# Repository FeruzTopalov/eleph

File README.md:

# **ELEPH** - _Never Get Lost!_

> **Note**
> Development of this device has been finished, only bug-fixes in the FW are possible
> There is an improved version of this device being under development, please see <https://github.com/FeruzTopalov/spoke>

<p align="center">
  <i>Dedicated to my friend Alexander Sadaev, rock climber.</i>
</p>

Eleph is a GPS-based Local Relative Navigation System (LRNS) for group of up to 6 members. It allows you to share your positional data in **real-time** among other Eleph-devices and navigate to each of them in a relative manner by providing **Distance** and **Azimuth** information - like RADAR does.

## Demonstration

Before diving into the details, watch the demo on **YouTube**: <https://youtu.be/EMacKdg9Z_0>

## Problem & Solution

As long as you stay under cell-coverage a navigation, either absolute or relative, is not a problem at all. You just use your phone with maps and messengers to find or share locations. Things change when you go off-grid. Hiking, skiing, sailing or whatever outdoor activity are a potential place to lose sight of your teammates. How to navigate in the group? Hopefully, there are couple of solutions available on the market:

* [LynQ](https://lynqme.com/pages/dev-consumer)
* [XQUAD](https://www.indiegogo.com/projects/xquad-smart-location-tracking-without-phones#/)
* [GoFindMe](https://www.indiegogo.com/projects/gofindme-a-gps-tracker-works-without-cell-service/#/)
* [GoTenna](https://gotennamesh.com/products/mesh)
* Also [GARMIN Dog collar](https://buy.garmin.com/en-US/US/c12522-p1.html)
* Also any [AIS](https://en.wikipedia.org/wiki/Automatic_identification_system) system

unfortunately all of them are commercial. But not the **Eleph**! 

**Eleph** is _open-source/open-hardware_ device which contains all major features needed for group navigation, such as:

* Detailed absolute positional information about each device in group
* RADAR-like interface with relative positional information about each device in group
* Memory slots to hold the position of any device and navigate it later
* GeoFence feature
* Timeout feature
* Alarm button

Due to open-source and simple and cheap hardware, Eleph is highly flexible solution that could be adapted to any use case you want:

* Hiking
* Climbing
* Sailing
* Hunting with the dogs
* Assets tracking
* and more...

## Technology

Eleph is written in pure C and runs on STM32 microcontroller. It has GPS module to receive positional data and synchronization signal, radio transceiver to exchange with radio packets between other devices, graphical display to show information on it, EEPROM memory IC to store coordinates, tactile buttons to control the device, buzzer to notify about events and couple of LEDs.

GPS module provides NMEA-0183 stream at 9600 baud. Microcontroller process the stream using DMA and parse it. Fields being extracted are RMC, GGA, GSA, GSV. Those give us information about time, date, latitude, longitude, speed, course, altitude, satellites in view and in use, navigation mode and validness of data.

GPS module also provides time synchronization signal - PPS. It is used as a time reference for the transmitting and receiving radio packets inside a current group of devices. Each group operates at the specific frequency channel, the way like regular radios. Each device in a group has unique predefined number from 1 to 6, so there are 6 members in a group maximum. Eleph uses TDMA technique to give channel access for each group member, so the device number corresponds to the time-slot occupied by device. There are 125 ms timer which starts counting from the rise of the PPS pulse. First 125 ms time-slot is used to parse and prepare positional data of the device. Next six time-slots are used to exchange with the positional data between devices via radio. A device is in TX state when time-slot number is equal to the device number, and in RX state otherwise. Remaining time before next PPS is reserved for relative positions calculation and displaying the results.

Eleph uses FSK transceiver and operates in LPD 433 MHz band (please make sure you are allowed to use those frequencies in your region, change otherwise). Data rate is 2400 bps, deviation is 2400 Hz (mod index = 2), channel spacing is 25 kHz. Packet structure is shown below. It consist of 29 bytes total and takes ~97 ms to be transmitted over-the-air.

In order to calculate relative positions of other devices, Eleph uses two formulas. First one is [Haversine formula](https://en.wikipedia.org/wiki/Haversine_formula) which determines the distance between two points on a sphere. The second one is [Loxodrome formula](https://en.wikipedia.org/wiki/Rhumb_line) which determines bearing to a point on a sphere relative to true north. All calculations are performed with a highest possible, double precision, so the results are in a great agreement with my simulations on PC. Precision of the formulas is another matter. It is known that haversine formula is numerically better-conditioned for small distances, but on the other side it doesn't take into account ellipsoidness of the Earth and uses it's mean radius. Also it is known that loxodrome (or rhumb line) shows not-the-shortest way to reach point of interest (the shortest way is provided by orthodrome, or great circle route), but the constant bearing, which is more useful in practice. Anyway, my simulations using Google Earth Pro ruler leave me no concerns about accuracy of used formulas. According to them the error for both is less than 1% as long as the distance is smaller than 300 km (!).

<p align="center">
  <i>(courtesy of <a href="https://www.esri.com/arcgis-blog/products/product/mapping/mercators-500th-birthday/">ESRI</a>)</i>
</p>

---

## FAQ

* _**Why is it called Eleph?**_ -Eleph stands for elephant. Elephants are a social animals, they form close bonds and stay in-touch - that is the main aim of the Eleph device.
* _**Why no LoRa yet?**_ -Believe or not, but i see no reason to use LoRa in the Eleph right now. Mainly due to low data rate. Probably next time, when i shorten payload, i will switch to LoRa mode.
* _**Why there is no compass?**_ -When i started the project i thought that COG (Course over Ground) information from the GPS would be enough, and that the COG relates to the true north, while compass gives magnetic north. Obviously information about true north is more valuable. The drawback for now is that COG requires you to move, there is no way to find the direction standing still.
* _**Any plans to resume the project?**_ -Next milestone is to rework user interface, make it simpler; refuse from excessive payload information, leaving just Lat/Lon data; update schematic/hardware. 
* _**How can i support the project?**_ -Eleph really needs your support. Main functionality is tested, but full and comprehensive outdoor tests are nor performed well yet. You could build it, test it on your side and report an issue if so - that is the best way to support.

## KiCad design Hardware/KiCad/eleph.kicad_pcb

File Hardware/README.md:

# Eleph Hardware
This folder contains hardware design of the ELEPH

## Design files
In the "**KiCad**" folder you can find KiCad project of the Eleph.

## Schematic
In the "**Schematic**" folder you can find PDF file with the schematic diagram.

## Production files
In the "**Gerbers**" folder you can find production files of Eleph.

## Hardware Notes
Couple of words about power supply. Supply chain is **_Single 18650 -> LDO 3.3V_**. I found no reason to put DC/DC because in common they have 80%-90% of efficiency, while LDO has ~78% in worst case (3.3V / 4.2V = 0.78). Do the increased complexity and cost worth several percent of efficiency? I do not think so.

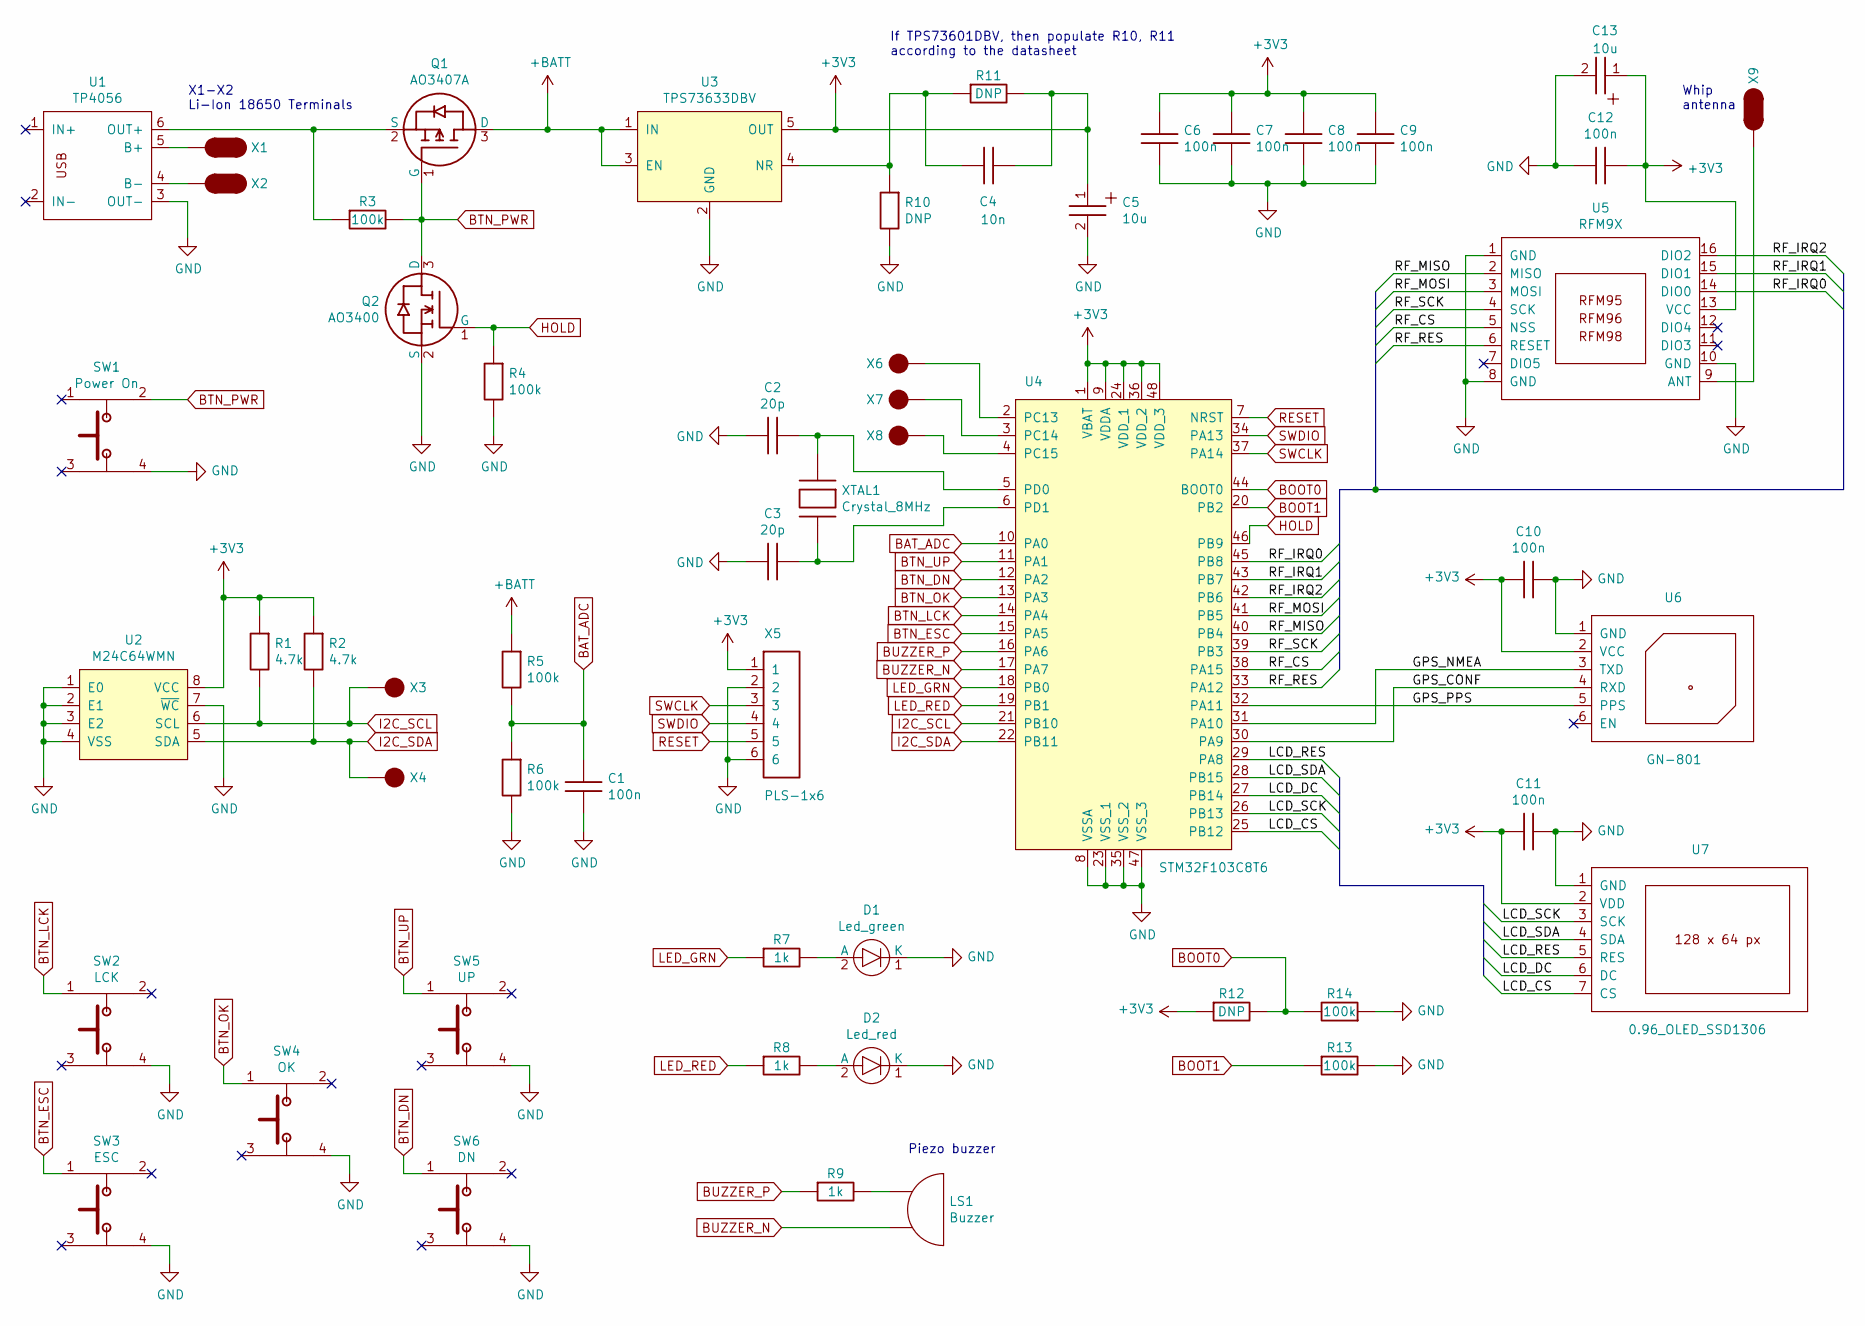
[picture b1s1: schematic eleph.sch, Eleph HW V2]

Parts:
C1, C6, C7, C8, C9, C10, C11, C12: 100n; C0805
C2, C3: 20p; C0805
C4: 10n; C0805
C5, C13: 10u; C_tantA
D1: Led_green; D1206
D2: Led_red; D1206
LS1: Buzzer; Buzzer_pitch7.6mm
Q1: AO3407A; SOT-23
Q2: AO3400; SOT-23
R1, R2: 4.7k; R0805
R3, R4, R5, R6, R13, R14: 100k; R0805
R7, R8, R9: 1k; R0805
R10, R11, R12: DNP; R0805
SW1: Power On; 52x52switch_smd_lowprofile
SW2: LCK; 6x6switch_smd
SW3: ESC; 6x6switch_smd
SW4: OK; 6x6switch_smd
SW5: UP; 6x6switch_smd
SW6: DN; 6x6switch_smd
U1: TP4056
U2: M24C64WMN; SOIC-8
U3: TPS73633DBV; SOT-23-5
U4: STM32F103C8T6; LQFP-48
U5: RFM9X
U6: GN-801
U7: 0.96_OLED_SSD1306; 0.96_OLED_SSD1306_7pin
X1, X2: Pad_oval
X3, X4, X6, X7, X8: Pad_round
X5: PLS-1x6; 1x6header
X9: Pad_oval; Antenna_terminal
XTAL1: Crystal_8MHz; HC49SM

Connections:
+3V3: C4.1, C5.1, C6.1, C7.1, C8.1, C9.1, C10.1, C11.1, C12.2, C13.1, R1.1, R2.1, R11.2, R12.1, U2.8 (VCC), U3.5 (OUT), U4.1 (VBAT), U4.9 (VDDA), U4.24 (VDD_1), U4.36 (VDD_2), U4.48 (VDD_3), U5.13 (VCC), U6.2 (VCC), U7.2 (VDD), X5.1
+BATT: Q1.3 (D), R5.1, U3.1 (IN), U3.3 (EN)
/GPS_CONF: U4.30 (PA9), U6.4 (RXD)
/GPS_NMEA: U4.31 (PA10), U6.3 (TXD)
/GPS_PPS: U4.32 (PA11), U6.5 (PPS)
/LCD_CS: U4.25 (PB12), U7.7 (CS)
/LCD_DC: U4.27 (PB14), U7.6 (DC)
/LCD_RES: U4.29 (PA8), U7.5 (RES)
/LCD_SCK: U4.26 (PB13), U7.3 (SCK)
/LCD_SDA: U4.28 (PB15), U7.4 (SDA)
/RF_CS: U4.38 (PA15), U5.5 (NSS)
/RF_IRQ0: U4.45 (PB8), U5.14 (DIO0)
/RF_IRQ1: U4.43 (PB7), U5.15 (DIO1)
/RF_IRQ2: U4.42 (PB6), U5.16 (DIO2)
/RF_MISO: U4.40 (PB4), U5.2 (MISO)
/RF_MOSI: U4.41 (PB5), U5.3 (MOSI)
/RF_RES: U4.33 (PA12), U5.6 (RESET)
/RF_SCK: U4.39 (PB3), U5.4 (SCK)
BAT_ADC: C1.1, R5.2, R6.1, U4.10 (PA0)
BOOT0: R12.2, R14.2, U4.44 (BOOT0)
BOOT1: R13.1, U4.20 (PB2)
BTN_DN: SW6.1, U4.12 (PA2)
BTN_ESC: SW3.1, U4.15 (PA5)
BTN_LCK: SW2.1, U4.14 (PA4)
BTN_OK: SW4.1, U4.13 (PA3)
BTN_PWR: Q1.1 (G), Q2.3 (D), R3.2, SW1.2
BTN_UP: SW5.1, U4.11 (PA1)
BUZZER_N: LS1.2, U4.17 (PA7)
BUZZER_P: R9.1, U4.16 (PA6)
GND: C1.2, C2.1, C3.1, C5.2, C6.2, C7.2, C8.2, C9.2, C10.2, C11.2, C12.1, C13.2, D1.1 (K), D2.1 (K), Q2.2 (S), R4.2, R6.2, R10.2, R13.2, R14.1, SW1.4, SW2.4, SW3.4, SW4.4, SW5.4, SW6.4, U1.3 (OUT-), U2.1 (E0), U2.2 (E1), U2.3 (E2), U2.4 (VSS), U2.7 (~WC), U3.2 (GND), U4.8 (VSSA), U4.23 (VSS_1), U4.35 (VSS_2), U4.47 (VSS_3), U5.1 (GND), U5.8 (GND), U5.10 (GND), U6.1 (GND), U7.1 (GND), X5.2, X5.6
HOLD: Q2.1 (G), R4.1, U4.46 (PB9)
I2C_SCL: R1.2, U2.6 (SCL), U4.21 (PB10), X3.1
I2C_SDA: R2.2, U2.5 (SDA), U4.22 (PB11), X4.1
LED_GRN: R7.1, U4.18 (PB0)
LED_RED: R8.1, U4.19 (PB1)
unnamed: C2.2, U4.5 (PD0), XTAL1.1
unnamed: C3.2, U4.6 (PD1), XTAL1.2
unnamed: C4.2, R10.1, R11.1, U3.4 (NR)
unnamed: D1.2 (A), R7.2
unnamed: D2.2 (A), R8.2
unnamed: LS1.1, R9.2
unnamed: Q1.2 (S), R3.1, U1.6 (OUT+)
unnamed: U1.4 (B-), X2.1
unnamed: U1.5 (B+), X1.1
unnamed: U4.2 (PC13), X6.1
unnamed: U4.3 (PC14), X7.1
unnamed: U4.4 (PC15), X8.1
unnamed: U5.9 (ANT), X9.1
RESET: U4.7 (NRST), X5.5
SWCLK: U4.37 (PA14), X5.3
SWDIO: U4.34 (PA13), X5.4

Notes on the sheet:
X1-X2 Li-Ion 18650 Terminals
If TPS73601DBV, then populate R10, R11 according to the datasheet
Whip antenna
Piezo buzzer

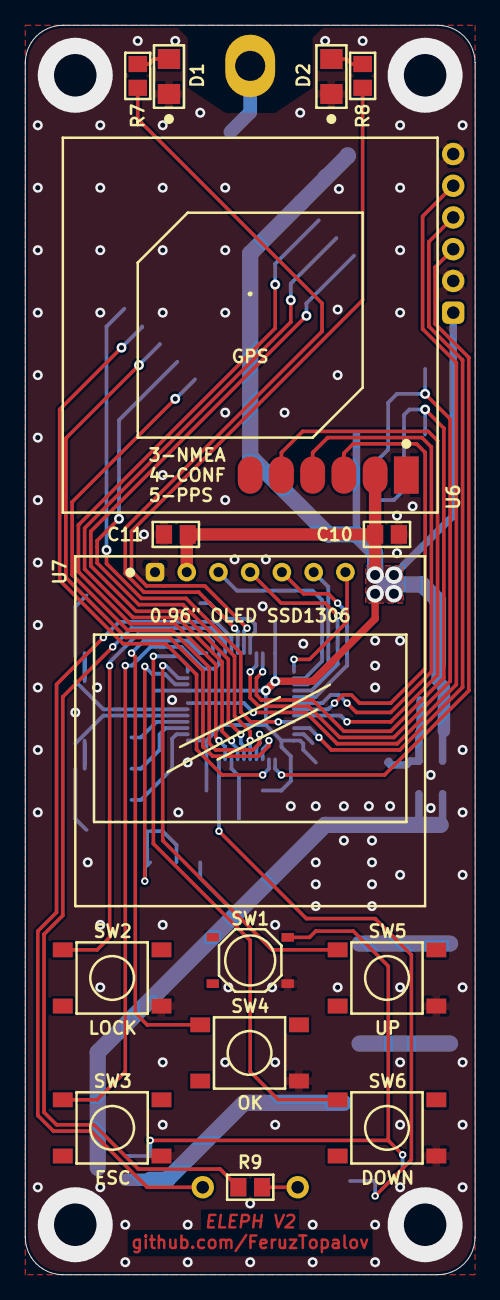
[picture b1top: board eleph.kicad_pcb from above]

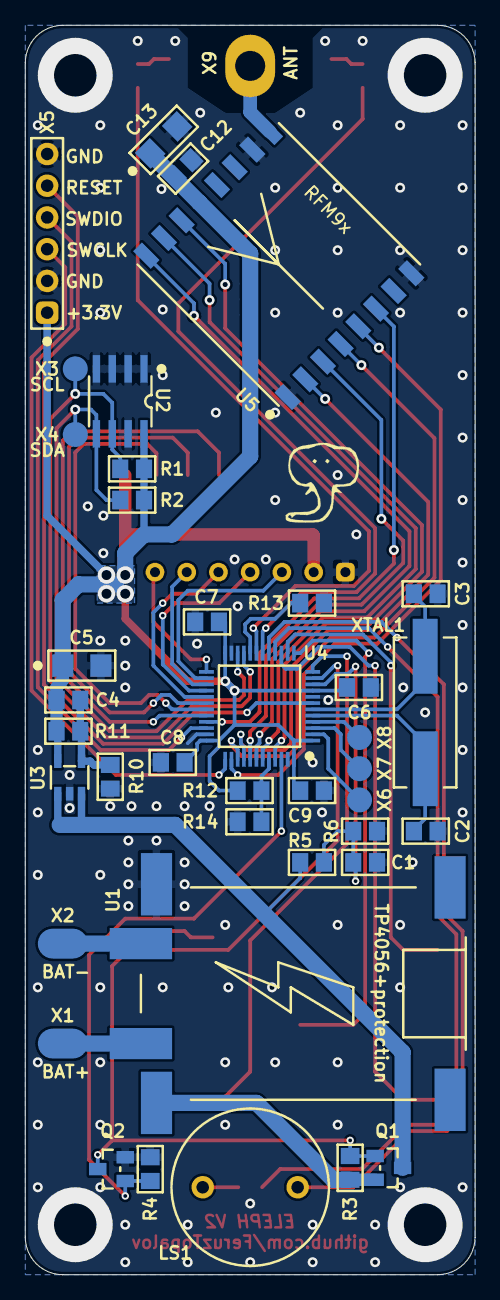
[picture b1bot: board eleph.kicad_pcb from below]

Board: 2 copper layers, 36.0 x 100.0 mm, 55 parts (40 on the bottom side), 51 nets.

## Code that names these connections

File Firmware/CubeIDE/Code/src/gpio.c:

/*
    ELEPH - Local Relative Navigation System <https://github.com/FeruzTopalov/eleph/>

	Copyright (C) 2021 Feruz Topalov
	Released under the GNU General Public License v3.0 <https://www.gnu.org/licenses/>
    
    file: gpio.c
*/



#include "stm32f10x.h"
#include "gpio.h"



//Initialization of all used ports
void gpio_init(void)
{
    //Port A
    RCC->APB2ENR |= RCC_APB2ENR_IOPAEN;
    
    //PA0 - ADC0 (Battery voltage)
    GPIOA->CRL &= ~GPIO_CRL_MODE0;      //input mode
    GPIOA->CRL &= ~GPIO_CRL_CNF0;       //analog input
    
    //PA1 - Button UP
    GPIOA->CRL &= ~GPIO_CRL_MODE1;      //input mode
    GPIOA->CRL &= ~GPIO_CRL_CNF1_0;     //input with pull
    GPIOA->CRL |= GPIO_CRL_CNF1_1; 
    GPIOA->ODR |= GPIO_ODR_ODR1;        //pull-up on
    
    //PA2 - Button DOWN
    GPIOA->CRL &= ~GPIO_CRL_MODE2;      //input mode
    GPIOA->CRL &= ~GPIO_CRL_CNF2_0;     //input with pull
    GPIOA->CRL |= GPIO_CRL_CNF2_1; 
    GPIOA->ODR |= GPIO_ODR_ODR2;        //pull-up on
    
    //PA3 - Button OK
    GPIOA->CRL &= ~GPIO_CRL_MODE3;      //input mode
    GPIOA->CRL &= ~GPIO_CRL_CNF3_0;     //input with pull
    GPIOA->CRL |= GPIO_CRL_CNF3_1; 
    GPIOA->ODR |= GPIO_ODR_ODR3;        //pull-up on
    
    //PA4 - Button LOCK
    GPIOA->CRL &= ~GPIO_CRL_MODE4;      //input mode
    GPIOA->CRL &= ~GPIO_CRL_CNF4_0;     //input with pull
    GPIOA->CRL |= GPIO_CRL_CNF4_1; 
    GPIOA->ODR |= GPIO_ODR_ODR4;        //pull-up on
    
    //PA5 - Button ESC
    GPIOA->CRL &= ~GPIO_CRL_MODE5;      //input mode
    GPIOA->CRL &= ~GPIO_CRL_CNF5_0;     //input with pull
    GPIOA->CRL |= GPIO_CRL_CNF5_1; 
    GPIOA->ODR |= GPIO_ODR_ODR5;        //pull-up on
    
    //PA6 - Piezo Buzzer (PWM) P
    GPIOA->CRL &= ~GPIO_CRL_MODE6_0;    //output 2 MHz
    GPIOA->CRL |= GPIO_CRL_MODE6_1;
    GPIOA->CRL &= ~GPIO_CRL_CNF6;       //alternate output push-pull
    GPIOA->CRL |= GPIO_CRL_CNF6_1;

    //PA7 - Piezo Buzzer (PWM) N
    GPIOA->CRL &= ~GPIO_CRL_MODE7_0;  	//output 2 MHz
    GPIOA->CRL |= GPIO_CRL_MODE7_1;
    GPIOA->CRL &= ~GPIO_CRL_CNF7_0;    	//alternate output push-pull
    GPIOA->CRL |= GPIO_CRL_CNF7_1;

    //PA8 - RES (SSD1306)
    GPIOA->CRH &= ~GPIO_CRH_MODE8_0;    //output 2 MHz
    GPIOA->CRH |= GPIO_CRH_MODE8_1;
    GPIOA->CRH &= ~GPIO_CRH_CNF8;      	//output push-pull
    
    //PA9 - USART TX1 (GPS config)
    GPIOA->CRH &= ~GPIO_CRH_MODE9_0;    //output 2 MHz
    GPIOA->CRH |= GPIO_CRH_MODE9_1;
    GPIOA->CRH &= ~GPIO_CRH_CNF9_0;     //alternate output push-pull
    GPIOA->CRH |= GPIO_CRH_CNF9_1;
    
    //PA10 - USART RX1 (GPS NMEA stream)
    GPIOA->CRH &= ~GPIO_CRH_MODE10;     //input
    GPIOA->CRH |= GPIO_CRH_CNF10_0;     //alternate input floating
    GPIOA->CRH &= ~GPIO_CRH_CNF10_1;
    
    //PA11 - GPS (PPS interrupt)
    GPIOA->CRH &= ~GPIO_CRH_MODE11;     //input mode
    GPIOA->CRH &= ~GPIO_CRH_CNF11_0;    //input with pull
    GPIOA->CRH |= GPIO_CRH_CNF11_1; 
    GPIOA->ODR &= ~GPIO_ODR_ODR11;      //pull-down
    
    //PA12 - RF Reset
    //GPIOA->CRH &= ~GPIO_CRH_MODE12_0;   //output 2 MHz
    //GPIOA->CRH |= GPIO_CRH_MODE12_1;
    //GPIOA->CRH &= ~GPIO_CRH_CNF12;		//output push-pull
    
    //PA15 - RF Chip Select
    GPIOA->CRH &= ~GPIO_CRH_MODE15_0;   //output 2 MHz
    GPIOA->CRH |= GPIO_CRH_MODE15_1;
    GPIOA->CRH &= ~GPIO_CRH_CNF15;      //output push-pull
    
    

    //Port B
    RCC->APB2ENR |= RCC_APB2ENR_IOPBEN;
    
    //PB0 - Green LED
    GPIOB->CRL &= ~GPIO_CRL_MODE0_0;    //output 2 MHz
    GPIOB->CRL |= GPIO_CRL_MODE0_1;
    GPIOB->CRL &= ~GPIO_CRL_CNF0;       //output push-pull
    
    //PB1 - Red LED
    GPIOB->CRL &= ~GPIO_CRL_MODE1_0;    //output 2 MHz
    GPIOB->CRL |= GPIO_CRL_MODE1_1;
    GPIOB->CRL &= ~GPIO_CRL_CNF1;       //output push-pull
    
    //PB3 - RF Clock
    GPIOB->CRL &= ~GPIO_CRL_MODE3_0;    //output 2 MHz
    GPIOB->CRL |= GPIO_CRL_MODE3_1;
    GPIOB->CRL &= ~GPIO_CRL_CNF3_0;     //alternate output push-pull
    GPIOB->CRL |= GPIO_CRL_CNF3_1;
    
    //PB4 - RF MISO
    GPIOB->CRL &= ~GPIO_CRL_MODE4;      //input mode
    GPIOB->CRL |= GPIO_CRL_CNF4_0;      //floating input
    GPIOB->CRL &= ~GPIO_CRL_CNF4_1;
    
    //PB5 - RF MOSI
    GPIOB->CRL &= ~GPIO_CRL_MODE5_0;    //output 2 MHz
    GPIOB->CRL |= GPIO_CRL_MODE5_1;
    GPIOB->CRL &= ~GPIO_CRL_CNF5_0;     //alternate output push-pull
    GPIOB->CRL |= GPIO_CRL_CNF5_1;
    
    //PB6 - RF IRQ2
    GPIOB->CRL &= ~GPIO_CRL_MODE6;      //input mode
    GPIOB->CRL &= ~GPIO_CRL_CNF6_0;     //input with pull
    GPIOB->CRL |= GPIO_CRL_CNF6_1;
    GPIOB->ODR |= GPIO_ODR_ODR6;        //pull-up
    
    //PB7 - RF IRQ1
    GPIOB->CRL &= ~GPIO_CRL_MODE7;      //input mode
    GPIOB->CRL &= ~GPIO_CRL_CNF7_0;     //input with pull
    GPIOB->CRL |= GPIO_CRL_CNF7_1;
    GPIOB->ODR |= GPIO_ODR_ODR7;        //pull-up

    //PB8 - RF IRQ0
    GPIOB->CRH &= ~GPIO_CRH_MODE8;      //input mode
    GPIOB->CRH &= ~GPIO_CRH_CNF8_0;     //input with pull
    GPIOB->CRH |= GPIO_CRH_CNF8_1;
    GPIOB->ODR |= GPIO_ODR_ODR8;        //pull-up

    //PB9 - Power Switch
    GPIOB->CRH &= ~GPIO_CRH_MODE9_0;   	//output 2 MHz
    GPIOB->CRH |= GPIO_CRH_MODE9_1;
    GPIOB->CRH &= ~GPIO_CRH_CNF9;		//output push-pull
    
    //PB10 - I2C SCL
    GPIOB->CRH &= ~GPIO_CRH_MODE10_0;   //output 2 MHz
    GPIOB->CRH |= GPIO_CRH_MODE10_1;
    GPIOB->CRH |= GPIO_CRH_CNF10;       //alternate function open-drain
    
    //PB11 - I2C SDA
    GPIOB->CRH &= ~GPIO_CRH_MODE11_0;   //output 2 MHz
    GPIOB->CRH |= GPIO_CRH_MODE11_1;
    GPIOB->CRH |= GPIO_CRH_CNF11;       //alternate function open-drain
    
    //PB12 - CS (SSD1306)
    GPIOB->CRH &= ~GPIO_CRH_MODE12_0;   //output 2 MHz
    GPIOB->CRH |= GPIO_CRH_MODE12_1;
    GPIOB->CRH &= ~GPIO_CRH_CNF12;      //output push-pull
    
    //PB13 - SCK (SSD1306)
    GPIOB->CRH &= ~GPIO_CRH_MODE13_0;   //output 2 MHz
    GPIOB->CRH |= GPIO_CRH_MODE13_1;
    GPIOB->CRH &= ~GPIO_CRH_CNF13_0;    //alternate output push-pull
    GPIOB->CRH |= GPIO_CRH_CNF13_1;
    
    //PB14 - D/C (SSD1306)
    GPIOB->CRH &= ~GPIO_CRH_MODE14_0;   //output 2 MHz
    GPIOB->CRH |= GPIO_CRH_MODE14_1;
    GPIOB->CRH &= ~GPIO_CRH_CNF14;      //output push-pull
    
    //PB15 - MOSI (SSD1306)
    GPIOB->CRH &= ~GPIO_CRH_MODE15_0;   //output 2 MHz
    GPIOB->CRH |= GPIO_CRH_MODE15_1;
    GPIOB->CRH &= ~GPIO_CRH_CNF15_0;    //alternate output push-pull
    GPIOB->CRH |= GPIO_CRH_CNF15_1;
}



//Init external interrupts
void ext_int_init(void)
{
    RCC->APB2ENR |= RCC_APB2ENR_AFIOEN;         //enable afio clock
    
    //PA11 - GPS PPS interrupt on rising edge
    AFIO->EXTICR[2] |= AFIO_EXTICR3_EXTI11_PA;  //exti 11 source is port A
    EXTI->RTSR |= EXTI_RTSR_TR11;               //interrupt 11 on rising edge
    EXTI->IMR |= EXTI_IMR_MR11;                 //unmask interrupt 11
    NVIC_EnableIRQ(EXTI15_10_IRQn);             //enable interrupt

    //PB8 - IRQ0 interrupt on rising edge
    AFIO->EXTICR[2] |= AFIO_EXTICR3_EXTI8_PB;	//exti 8 source is port B
    EXTI->RTSR |= EXTI_RTSR_TR8;				//interrupt 8 on rising edge
    EXTI->IMR |= EXTI_IMR_MR8;					//unmask interrupt 8

    NVIC_EnableIRQ(EXTI9_5_IRQn);               //enable IRQn interrupts

    EXTI->PR = (uint32_t)0x0007FFFF;            //clear all pending interrupts
}



//Red led on
void led_red_on(void)
{
    GPIOB->BSRR = GPIO_BSRR_BS1;
}



//Red led off
void led_red_off(void)
{
    GPIOB->BSRR = GPIO_BSRR_BR1;
}



//Red green on
void led_green_on(void)
{
    GPIOB->BSRR = GPIO_BSRR_BS0;
}



//Red green off
void led_green_off(void)
{
    GPIOB->BSRR = GPIO_BSRR_BR0;
}



//RF CS active
void cs_rfm98_active(void)
{
    GPIOA->BSRR = GPIO_BSRR_BR15;
}



//RF CS inactive
void cs_rfm98_inactive(void)
{
    GPIOA->BSRR = GPIO_BSRR_BS15;
}



//RF RES active
void res_rfm98_active(void)
{


    GPIOA->CRH &= ~GPIO_CRH_MODE12_0;   //output 2 MHz
    GPIOA->CRH |= GPIO_CRH_MODE12_1;
    GPIOA->CRH &= ~GPIO_CRH_CNF12;		//output push-pull


    GPIOA->BSRR = GPIO_BSRR_BR12;
}



//RF RES inactive
void res_rfm98_inactive(void)
{
    GPIOA->CRH &= ~GPIO_CRH_MODE12;   	//input
    GPIOA->CRH &= ~GPIO_CRH_CNF12_1;	//float
    GPIOA->CRH |= GPIO_CRH_CNF12_0;
}



//RES SSD1306 active
void res_ssd1306_active(void)
{
    GPIOA->BSRR = GPIO_BSRR_BR8;
}



//RES SSD1306 inactive
void res_ssd1306_inactive(void)
{
    GPIOA->BSRR = GPIO_BSRR_BS8;
}



//Data mode SSD1306
void ssd1306_data_mode(void)
{
    GPIOB->BSRR = GPIO_BSRR_BS14;
}



//Command mode SSD1306
void ssd1306_command_mode(void)
{
    GPIOB->BSRR = GPIO_BSRR_BR14;
}



//CS SSD1306 active
void cs_ssd1306_active(void)
{
    GPIOB->BSRR = GPIO_BSRR_BR12;
}



//CS SSD1306 inactive
void cs_ssd1306_inactive(void)
{
    GPIOB->BSRR = GPIO_BSRR_BS12;
}



//Battery monitoring on
void hold_power(void)
{
    GPIOB->BSRR = GPIO_BSRR_BS9;
}



//Battery monitoring off
void release_power(void)
{
    GPIOB->BSRR = GPIO_BSRR_BR9;
}

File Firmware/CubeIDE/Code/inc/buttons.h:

/*
    ELEPH - Local Relative Navigation System <https://github.com/FeruzTopalov/eleph/>

	Copyright (C) 2021 Feruz Topalov
	Released under the GNU General Public License v3.0 <https://www.gnu.org/licenses/>
    
    file: buttons.h
*/



#ifndef BUTTONS_HEADER
#define BUTTONS_HEADER



#define BTN_NO_ACTION        (0)

#define BTN_UP               (1)     //PA1
#define BTN_UP_LONG          (2)

#define BTN_DOWN             (3)     //PA2
#define BTN_DOWN_LONG        (4)

#define BTN_OK               (5)     //PA3
#define BTN_OK_LONG          (6)

#define BTN_PWR              (7)     //PA4
#define BTN_PWR_LONG         (8)

#define BTN_ESC              (9)     //PA5
#define BTN_ESC_LONG         (10)



uint8_t scan_buttons(void);



#endif /*BUTTONS_HEADER*/

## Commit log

2021-02-14 Init folders structure, add readme files
2021-02-14 Add the Cube IDE project
2021-02-15 Update firmware readme
2021-02-17 Add schematic, hardware readme, hardware pictures
2021-02-17 Update hardware readme
2021-02-17 Update hardware readme x2
2021-03-03 Update all READMEs, load pictures, add WDS3 files
2021-04-10 Fix schematic diagram, add missed pull-ups at SDA, SCK pins
2021-04-10 Update CHANGELOG
2021-11-28 Upload KiCad project, source code, updated README files
